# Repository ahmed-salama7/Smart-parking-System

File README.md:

# Smart Parking System

> An automated parking-management prototype that detects vehicles with FC-51 IR
> sensors at the entrance and exit and controls access through a servo gate,
> driven by a finite-state-machine firmware on an Arduino Uno. Live occupancy is
> shown on an LCD with traffic-light feedback.

---

## Problem

Conventional parking lots give drivers no live information about availability —
you enter, search, and often find the lot full only after wasting time and fuel.
This project demonstrates an automated, low-cost alternative: a system that
tracks occupancy in real time, controls access automatically, and shows drivers
the number of free spaces at a glance.

---

## How It Works

- **Two FC-51 IR sensors** detect vehicles at the entrance and the exit
  (active-LOW digital output — LOW when a car breaks the beam).
- The system **counts cars in and out against a 4-space capacity** — it tracks
  total occupancy rather than sensing each individual bay.
- A **finite state machine** in firmware manages the full gate cycle:
  `idle → car detected → check capacity → open → pass-through → close`.
- An **SG90 servo** drives the entry/exit barrier (0° closed, 90° open).
- A **16×2 I²C LCD** displays live status — free-slot count and OPEN / FULL.
- A **traffic-light LED module** gives instant visual feedback
  (green = enter, yellow = gate moving, red = full).

*System schematic, designed in KiCad.*

---

## Key Components

- **Microcontroller:** Arduino Uno R3 (ATmega328P)
- **Sensors:** FC-51 IR obstacle sensors ×2 (entrance + exit)
- **Actuator:** TowerPro SG90 micro servo (gate barrier)
- **Display:** 16×2 character LCD with PCF8574 I²C backpack
- **Indicators:** Traffic-light LED module (R/Y/G)
- **Custom PCB:** carrier shield designed in KiCad (see [`/hardware`](hardware/))

Full bill of materials: [`docs/SmartParking_BOM.xlsx`](docs/SmartParking_BOM.xlsx).
Engineering write-up: [`docs/DESIGN_NOTES.md`](docs/DESIGN_NOTES.md).

---

## Hardware Design

A custom carrier PCB was designed in KiCad to move the project off breadboard
wiring. The full project files (schematic, board, and project) are in
[`/hardware`](hardware/).

*Custom PCB layout (KiCad).*

---

## Engineering Notes — From Simulation to Hardware

The control logic was first validated in a **Wokwi simulation**, then ported to
the physical board. That port was the most instructive part of the build:

- **Different sensors in simulation vs hardware.** Wokwi doesn't provide the
  FC-51 IR module, so the simulation uses **HC-SR04 ultrasonic** sensors while
  the real board ([`firmware/arduino_smart_parking_system_fc51.ino`](firmware/arduino_smart_parking_system_fc51.ino))
  uses **FC-51 IR**. The two detect vehicles differently as a result: the
  simulation reads an ultrasonic *distance* and compares it against a threshold,
  whereas the real board reads the FC-51's *digital beam-break* output directly.
- **Debouncing the IR input.** A raw IR module can blip on ambient light or a
  passing hand, so the firmware only accepts a vehicle after several consecutive
  "detected" reads — rejecting single-frame false triggers.
- **A gate safety timeout.** If a vehicle stalls in the beam or a sensor sticks
  on, the gate force-closes after a fixed timeout instead of hanging open and
  freezing the whole system.

---

## The System in Action

The physical prototype running a complete parking cycle — from an empty lot,
through vehicles entering, to a full lot denying access:

| | | |
|:--:|:--:|:--:|
|  |  |  |
| **Lot empty** — 4 slots free, gate down | **First car approaches**  | **Gate opens** — "Car entering..." |
|  |  |  |
| **Slot count drops** as cars are admitted | **Lot full** — 0 spaces available | **Access denied** — "No Space Left", red light |

---

## Simulation

The full control logic was validated in a Wokwi simulation before hardware
testing (sensor difference explained in *Engineering Notes* above).

*Wokwi simulation wiring (uses HC-SR04 in place of the FC-51 modules).*

[▶️ Watch the full simulation video](media/simulation-behavioral-demo-video.mp4)

---

## Repository Structure

```
Smart-parking-System/
├── firmware/
│   └── arduino_smart_parking_system_fc51.ino   Real board (FC-51 IR)
├── hardware/
│   ├── Smart Parking System.kicad_sch          KiCad schematic
│   ├── Smart Parking System.kicad_pcb          KiCad board layout
│   ├── Smart Parking System.kicad_pro          KiCad project
│   ├── schematic.png                           Schematic export
│   └── PCB layout.png                          PCB layout export
├── docs/
│   ├── DESIGN_NOTES.md                         Engineering write-up
│   └── SmartParking_BOM.xlsx                    Bill of materials
├── media/                                      Real-build photos, sim video/GIF
└── README.md
```

---

## Status

Working hardware prototype, 2026.

<!-- [VERIFY] Optional metric: "Detection accuracy 100% (entrance) / 95% (exit)
over 20 trials each." Keep this ONLY if you actually ran and logged these
trials. If you didn't, delete this comment entirely. -->

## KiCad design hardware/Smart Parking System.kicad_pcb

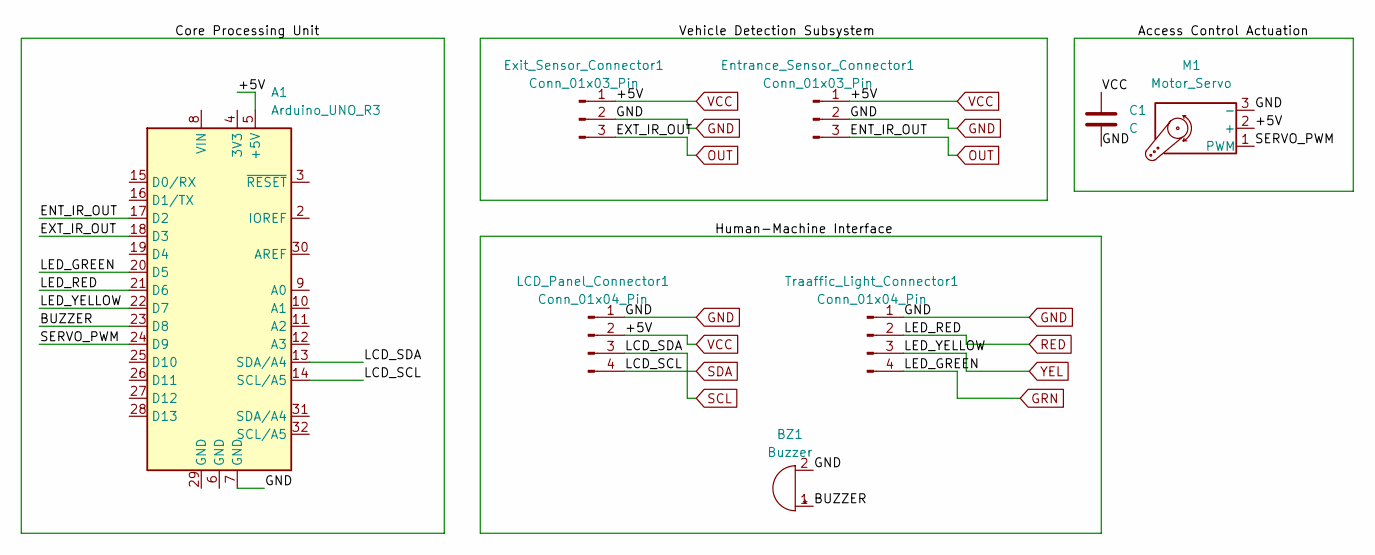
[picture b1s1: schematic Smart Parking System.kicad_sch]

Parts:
A1: Arduino_UNO_R3
BZ1: Buzzer; Buzzer_12x9.5RM7.6
C1: C; C_Elec_3x5.4
Entrance_Sensor_Connector1: Conn_01x03_Pin; FanPinHeader_1x03_P2.54mm_Vertical
Exit_Sensor_Connector1: Conn_01x03_Pin; FanPinHeader_1x03_P2.54mm_Vertical
LCD_Panel_Connector1: Conn_01x04_Pin; FanPinHeader_1x04_P2.54mm_Vertical
M1: Motor_Servo; PinHeader_1x03_P2.54mm_Horizontal
Traaffic_Light_Connector1: Conn_01x04_Pin; FanPinHeader_1x04_P2.54mm_Vertical

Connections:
/BUZZER: A1.23 (D8), BZ1.1 (+)
/SERVO_PWM: A1.24 (D9), M1.1 (PWM)
GND: A1.7 (GND), BZ1.2 (-), C1.2, Entrance_Sensor_Connector1.2, Exit_Sensor_Connector1.2, LCD_Panel_Connector1.1, M1.3 (-), Traaffic_Light_Connector1.1
GRN: A1.20 (D5), Traaffic_Light_Connector1.4
OUT: A1.17 (D2), A1.18 (D3), Entrance_Sensor_Connector1.3, Exit_Sensor_Connector1.3
RED: A1.21 (D6), Traaffic_Light_Connector1.2
SCL: A1.13 (SDA/A4), LCD_Panel_Connector1.3
SDA: A1.14 (SCL/A5), LCD_Panel_Connector1.4
VCC: A1.5 (+5V), C1.1, Entrance_Sensor_Connector1.1, Exit_Sensor_Connector1.1, LCD_Panel_Connector1.2, M1.2 (+)
YEL: A1.22 (D7), Traaffic_Light_Connector1.3

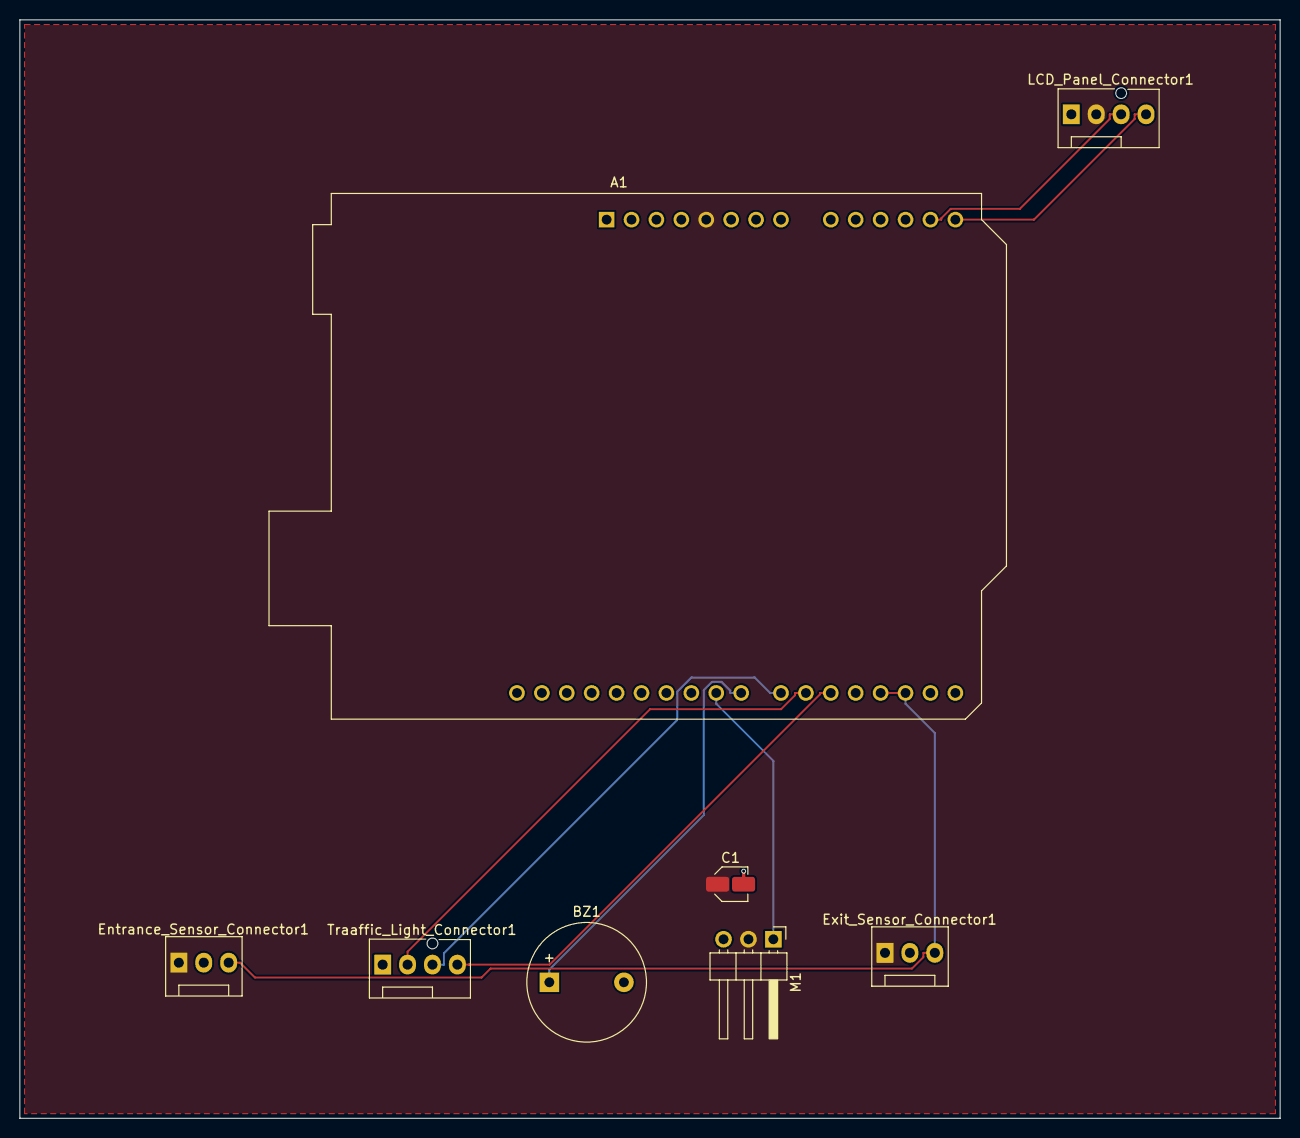
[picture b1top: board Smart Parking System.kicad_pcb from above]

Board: 2 copper layers, 128.5 x 112.0 mm, 8 parts (0 on the bottom side), 10 nets.

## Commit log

2026-06-19 Create Hardware
2026-06-25 Rename simulation-behavioral-demo.mp4 to simulation-behavioral-demo-video.mp4
2026-06-26 Refactor README for clarity and structure
    Updated README with improved formatting, added hardware design section, and clarified project details.
2026-06-26 Fix description for first car approaching
